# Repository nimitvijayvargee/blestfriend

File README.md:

---

this is a basic devboard I made to practice soldering SMD components better, as well as to help me create audio sink/source projects which I have plans for :3
it essentially uses an ESP32-WROOM-32E module, which supports wifi, BLE and BT classic,, which are all quite useful for general projects and iot applications. 

besides that, it's pretty much a standard ESP32 devboard with a UART link.

## PCB

# BOM
Here's a rough list of components you need to actually finish this! All SMD passives are 0805 unless specified otherwise

- PCB (1.6mm thickness FR4 2 Layer board, other settings up to your discretion!)
- USB C Receptacle (HRO TYPE-C-31-M-14)
- 2x BAT60A SOD323 Diodes
- AP1117-33 Linear Regulator SOT223-3
- ESP32-WROOM-32E OR ESP32-WROOM-32UE (UE needs external antenna)
- CH340C SOIC16 (Other CH340 variants needing a crystal will not work!)
- 6mm Tactile Push Button
Passives:
- 4x 100nF Ceramic Capacitors
- 4x 10uF Ceramic Capacitors
- 2x 100k Resistors
- 2x 200k Resistors
- 2x 5.1k Resistors (CC Pulldown)
- 1x 10k Resistor

You can also find a more thorough BOM with URLs for sellers in India in BOM.csv.

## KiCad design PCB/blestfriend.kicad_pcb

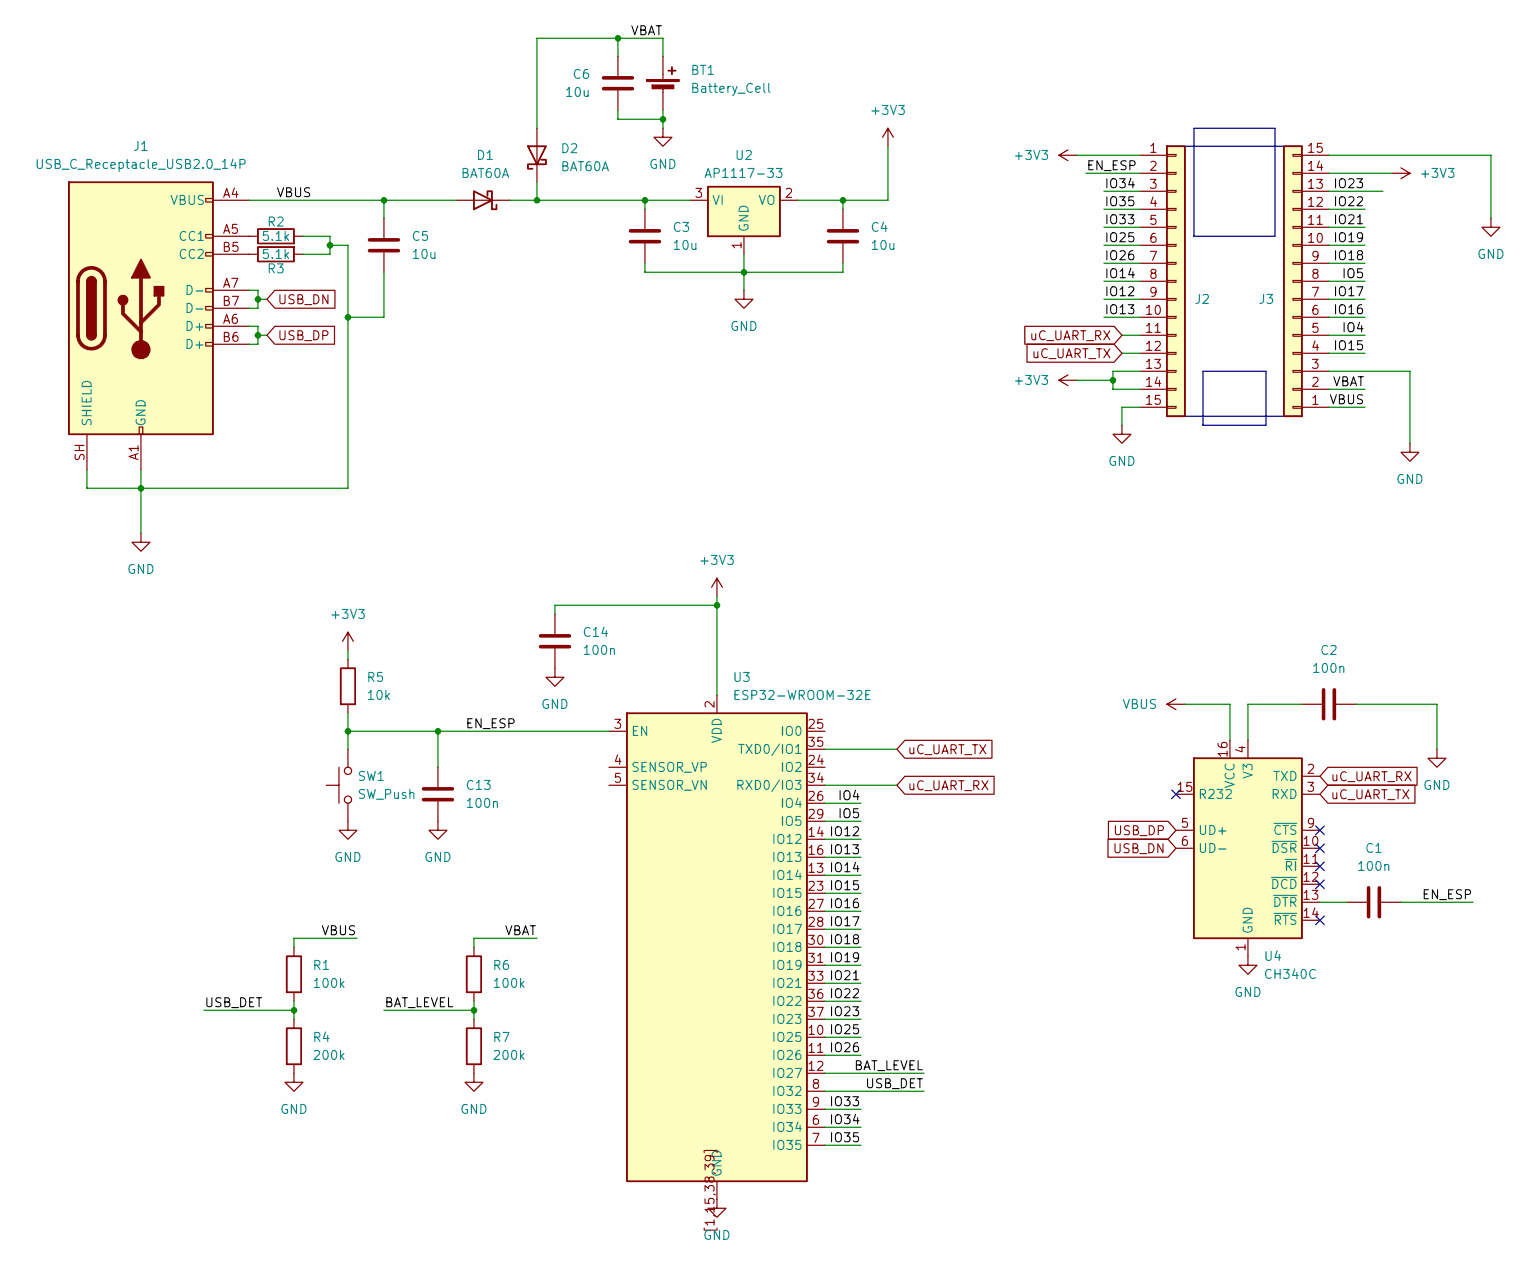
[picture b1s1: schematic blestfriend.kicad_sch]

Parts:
BT1: Battery_Cell
C1, C2, C13, C14: 100n; C_0805_2012Metric
C3, C4, C5, C6: 10u; C_0805_2012Metric
D1, D2: BAT60A; D_SOD-323
J1: USB_C_Receptacle_USB2.0_14P; USB_C_HRO_TYPE-C-31-M-14
J2, J3: Conn_01x15; PinHeader_1x15_P2.54mm_Vertical
R1, R6: 100k; R_0805_2012Metric
R2, R3: 5.1k; R_0805_2012Metric
R4, R7: 200k; R_0805_2012Metric
R5: 10k; R_0805_2012Metric
SW1: SW_Push; SW_PUSH_6mm
U2: AP1117-33; SOT-223-3_TabPin2
U3: ESP32-WROOM-32E
U4: CH340C; SOIC-16_3.9x9.9mm_P1.27mm

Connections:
+3V3: C4.1, C14.1, J2.1, J2.13, J2.14, J3.14, R5.1, U2.2 (VO), U3.2 (VDD)
/BAT_LEVEL: R6.2, R7.1, U3.12 (IO27)
/EN_ESP: C1.2, C13.1, J2.2, R5.2, SW1.2, U3.3 (EN); also elsewhere on the board
/IO4: J3.5, U3.26 (IO4)
/IO5: J3.8, U3.29 (IO5)
/IO12: J2.9, U3.14 (IO12)
/IO13: J2.10, U3.16 (IO13)
/IO14: J2.8, U3.13 (IO14)
/IO15: J3.4, U3.23 (IO15)
/IO16: J3.6, U3.27 (IO16)
/IO17: J3.7, U3.28 (IO17)
/IO18: J3.9, U3.30 (IO18)
/IO19: J3.10, U3.31 (IO19)
/IO21: J3.11, U3.33 (IO21)
/IO22: J3.12, U3.36 (IO22)
/IO23: J3.13, U3.37 (IO23)
/IO25: J2.6, U3.10 (IO25)
/IO26: J2.7, U3.11 (IO26)
/IO33: J2.5, U3.9 (IO33)
/IO34: J2.3, U3.6 (IO34)
/IO35: J2.4, U3.7 (IO35)
/USB_DET: R1.2, R4.1, U3.8 (IO32)
/VBAT: BT1.1 (+), C6.1, D2.2 (A), J3.2, R6.1
GND: BT1.2 (-), C2.2, C3.2, C4.2, C5.2, C6.2, C13.2, C14.2, J1.A1 (GND), J1.A12 (GND), J1.B1 (GND), J1.B12 (GND), J1.SH (SHIELD), J2.15, J3.3, J3.15, R2.2, R3.2, R4.2, R7.2, SW1.1, U2.1 (GND), U3.1 (GND), U3.15 (GND), U3.38 (GND), U3.39 (GND), U3.[1,15,38,39] (GND), U4.1 (GND); also elsewhere on the board
unnamed: C3.1, D1.1 (K), D2.1 (K), U2.3 (VI)
unnamed: J1.A5 (CC1), R2.1
unnamed: J1.B5 (CC2), R3.1
unnamed: C2.1, U4.4 (V3)
unnamed: C1.1, U4.13 (~DTR)
USB_DN: J1.A7 (D-), J1.B7 (D-), U4.6 (UD-)
USB_DP: J1.A6 (D+), J1.B6 (D+), U4.5 (UD+)
VBUS: C5.1, D1.2 (A), J1.A4 (VBUS), J1.A9 (VBUS), J1.B4 (VBUS), J1.B9 (VBUS), J3.1, R1.1, U4.16 (VCC)
uC_UART_RX: J2.11, U3.34 (RXD0/IO3), U4.2 (TXD)
uC_UART_TX: J2.12, U3.35 (TXD0/IO1), U4.3 (RXD)

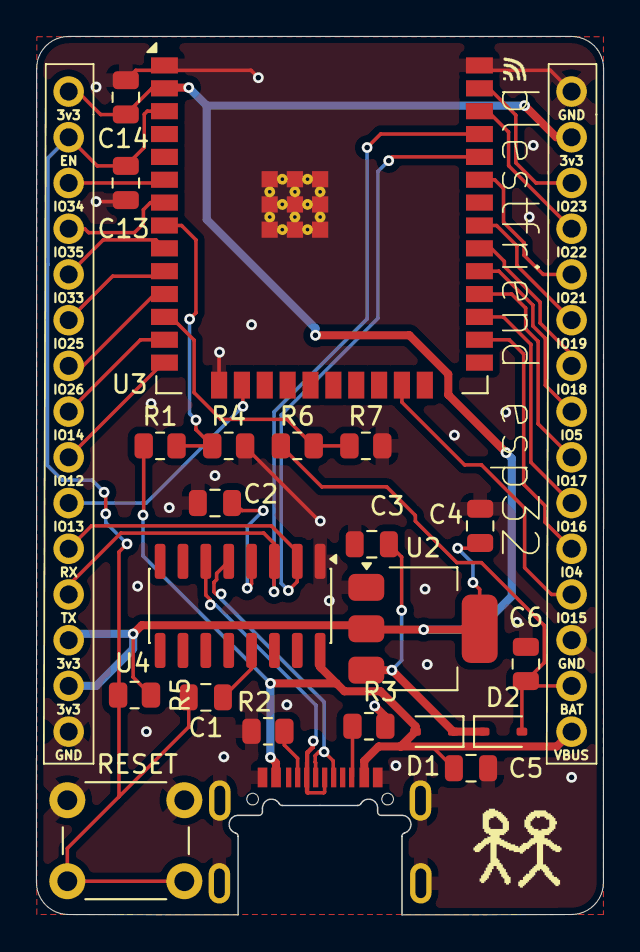
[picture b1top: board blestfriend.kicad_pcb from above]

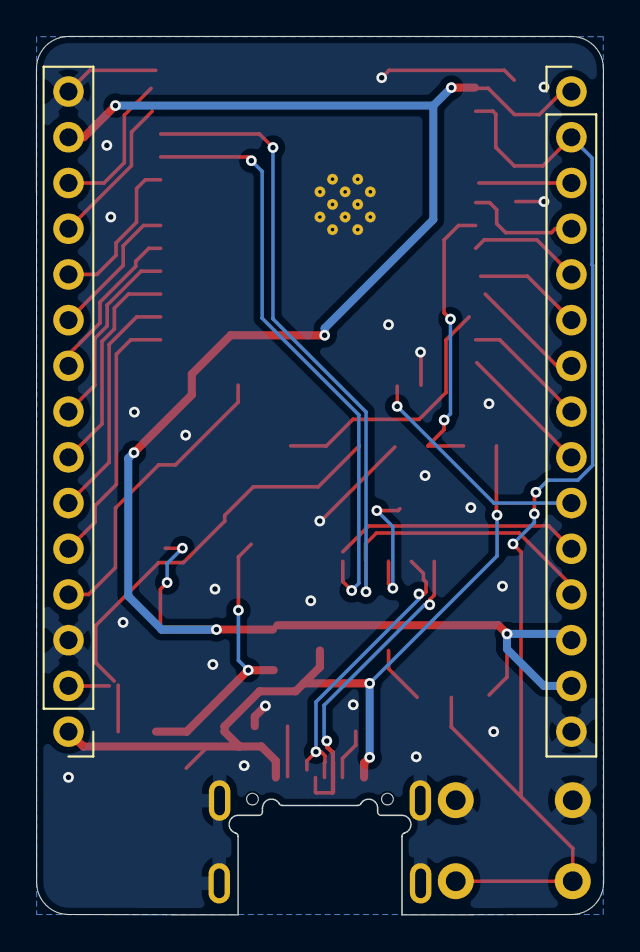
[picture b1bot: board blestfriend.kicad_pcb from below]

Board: 2 copper layers, 31.5 x 48.8 mm, 24 parts (2 on the bottom side), 34 nets.

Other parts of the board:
RESET: SW_Push; SW_PUSH_6mm

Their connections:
/EN_ESP: RESET.2; also elsewhere on the board
GND: RESET.1; also elsewhere on the board

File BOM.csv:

Item,Link,Quantity (1x PCB),Cost (1x PCB),Cost (5x PCB)
PCB,https://pcbpower.com/,1,10.32,51.61
USB Receptacle,https://robu.in/product/type-c-31-m-14-hroparts-1-16p-female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,1,0.68,3.39
BAT60A,https://robu.in/product/bat60a-slkor-10v-580mv1a-sod-323-sch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,2,0.22,1.08
AP1117-33,https://robu.in/product/ap1117e33g-13-1a-dropout-positive-ad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,1,0.12,0.59
ESP32-WROOM-32E-N8R2,https://robu.in/product/espressif-esp32-wroom-32e-n8r2-module/,1,4.73,23.64
CH340C,https://hubtronics.in/ch340c/,1,0.46,2.32
6mm Tactile Button,https://robu.in/product/tsd001a05026a-bzcn-6mm-5mm-50ma-roun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,1,0.02,0.11
100nF 0805,https://robu.in/product/cc0805kkx7r0bb104-yageo-100v-100nf-x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,4,0.06,0.32
10uF 0805,https://robu.in/product/0805x106k500nt-fh-50v-10uf-x5r%c2%b1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,4,0.26,1.29
200k 0805,https://robu.in/product/ac0805fr-07200kl-yageo-res-thick-fil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,2,0.01,0.03
100k 0805,https://robu.in/product/ac0805fr-7w100kl-yageo-res-thick-fil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,2,0.01,0.03
5.1k 0805,https://robu.in/product/erj6geyj512v-panasonic-125mw-thick-f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,2,0.02,0.11
10k 0805,https://robu.in/product/0805w8j0103t5e-uniohm-royal-ohm-125m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,1,0.01,0.04
Total,,,16.91,84.56
